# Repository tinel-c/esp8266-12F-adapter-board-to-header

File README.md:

# esp8266-12F adapter board to header

## Schematic

## PCB layout

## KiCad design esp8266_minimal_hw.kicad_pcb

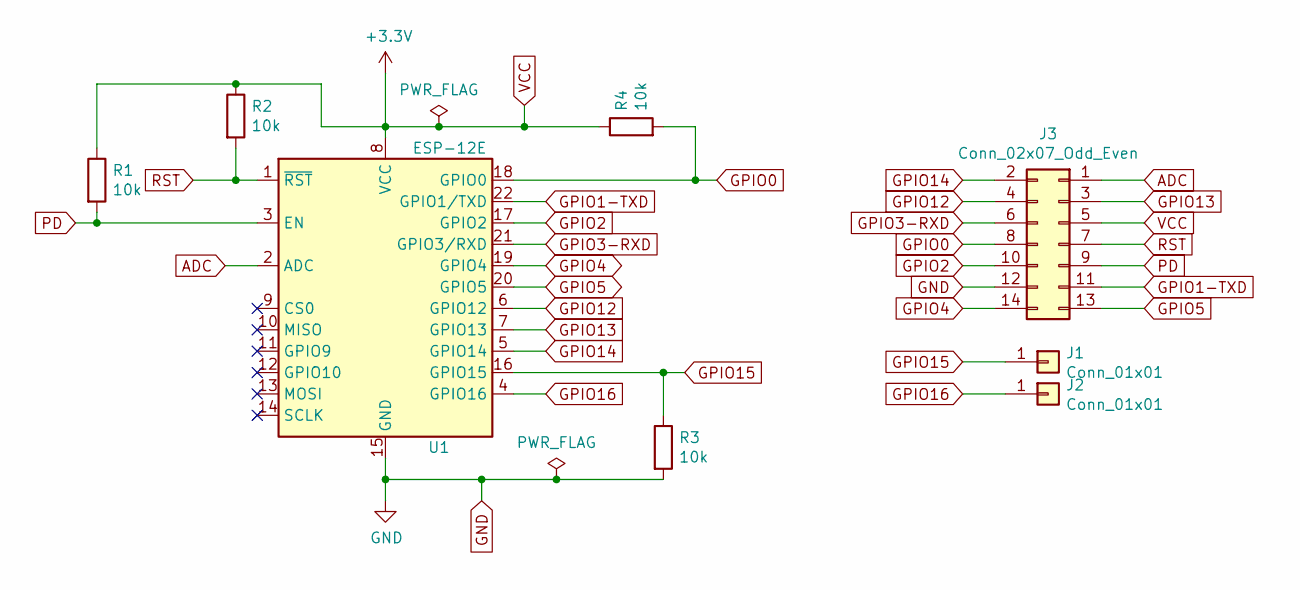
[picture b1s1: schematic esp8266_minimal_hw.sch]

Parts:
J1, J2: Conn_01x01; PinHeader_1x01_P2.54mm_Vertical
J3: Conn_02x07_Odd_Even; PinHeader_2x07_P2.54mm_Vertical
R1, R2, R3, R4: 10k; R_1206_3216Metric_Pad1.42x1.75mm_HandSolder
U1: ESP-12E

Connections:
ADC: J3.1, U1.2 (ADC)
GND: J3.12, R3.2, U1.15 (GND)
GPIO0: J3.8, R4.2, U1.18 (GPIO0)
GPIO1-TXD: J3.11, U1.22 (GPIO1/TXD)
GPIO2: J3.10, U1.17 (GPIO2)
GPIO3-RXD: J3.6, U1.21 (GPIO3/RXD)
GPIO4: J3.14, U1.19 (GPIO4)
GPIO5: J3.13, U1.20 (GPIO5)
GPIO12: J3.4, U1.6 (GPIO12)
GPIO13: J3.3, U1.7 (GPIO13)
GPIO14: J3.2, U1.5 (GPIO14)
GPIO15: J1.1, R3.1, U1.16 (GPIO15)
GPIO16: J2.1, U1.4 (GPIO16)
PD: J3.9, R1.2, U1.3 (EN)
RST: J3.7, R2.2, U1.1 (~RST)
VCC: J3.5, R1.1, R2.1, R4.1, U1.8 (VCC)

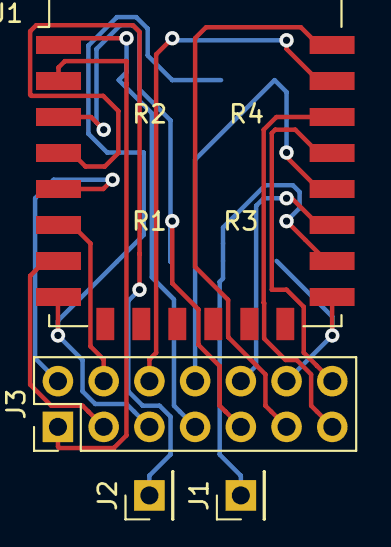
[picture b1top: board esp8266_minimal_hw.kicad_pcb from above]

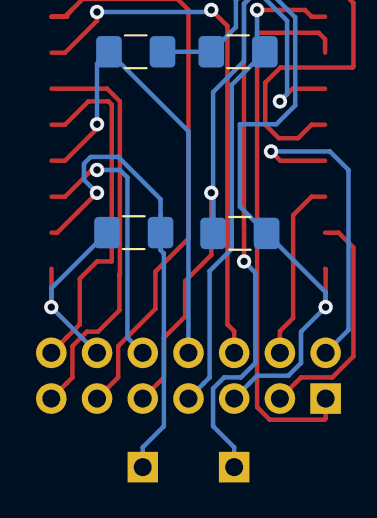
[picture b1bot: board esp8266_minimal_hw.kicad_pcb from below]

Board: 2 copper layers, 8 parts (4 on the bottom side), 16 nets.

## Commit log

2019-06-17 Initial commit for kicad design of adapter board
    This is the first design for the adapter board to header file.
